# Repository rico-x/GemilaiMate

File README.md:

# GemilaiMate

**Gemilai 3007Z · carrier v0.1 / shield v0.2.4 / Compact 0.3.1 · firmware v0.1.0 · Rico-X**

> **Проект пока не воспроизводился в железе. Ни одна плата не изготовлена и не собрана, USB-прошивка на реальных модулях и работа в кофемашине не проверялись. Успешные сборки, тесты и ERC/DRC относятся только к файлам и программным моделям.**

Самостоятельный проект адаптации управления проливом Gemilai 3007Z: ESP32-S3, LilyGo T-RGB 2.1, давление через ADS1115, термопара MAX31855, управление помпой через RobotDyn и клапаном через внешний SSR. Предполагается сохранение штатного управления нагревом и паром; применимость к конкретной машине ещё требует проверки. Сеть 230 В ни на одну из плат не заходит.

**Сайт проекта: [rico-x.github.io/GemilaiMate](https://rico-x.github.io/GemilaiMate/)** — все платы, схемы подключения с 3D, закупка и пошаговый монтаж Compact.

Разводка, исходники и производственные файлы находятся в этом репозитории; исходный проект не требуется для сборки. Обновления извне автоматически не подтягиваются, нужные изменения переносятся вручную после проверки.

## Три варианта платы

Варианты независимы: у каждого свой KiCad-проект и производственный комплект. GPIO и логика прошивки общие, отличаются компоновка, контроллер и способ сборки.

| | [Carrier v0.1](#carrier-v01) | [Shield v0.2.4](#shield-v024) | [Compact 0.3.1](#compact-031) |
|---|---|---|---|
| Текстолит | 90×46 мм, 2 слоя | 90×75 мм, 2 слоя | 76×61 мм, 2 слоя + антенна 7 мм |
| Контроллер | ESP32-S3 DevKit N8R8 в гнёздах | ESP32-S3 DevKit N8R8 в гнёздах | ESP32-S3-WROOM-1-N16R8 на плате |
| ADS1115 / MAX31855 / TXS0102 | на жгутах | в гнёздах | в гнёздах |
| Жгуты базовой машины | 9 жгутов, 37 проводов | 6 жгутов, 18 проводов | 6 жгутов, 18 проводов |
| SMD | 20 | 20 | 77, в том числе WROOM и USB-C |
| Цель прошивки | `controller`, ID=3 | `controller`, ID=3 | `controller-compact`, ID=4 |
| Подключение и 3D | [wiring.html](https://rico-x.github.io/GemilaiMate/wiring.html) | [shield-wiring.html](https://rico-x.github.io/GemilaiMate/shield-wiring.html) | [compact-wiring.html](https://rico-x.github.io/GemilaiMate/compact-wiring.html) |

## Carrier v0.1

Исходная плата 90×46 мм: DevKit в гнёздах, измерительные и силовые модули подключаются жгутами. Плата не изменялась с первого выпуска.

- [Подключение в машине: схема, 3D и жгуты](https://rico-x.github.io/GemilaiMate/wiring.html) ([файл](docs/wiring.html)).
- [Сборка и крепление](docs/assembly.md), [интерфейсы платы](docs/interfaces.md), [корпуса жгутов](docs/harnesses.md).
- [Комплектующие](docs/components.md) и [пример закупки комплекта](docs/purchase-kit.md).
- KiCad: [`hardware/carrier/gemilaimate-carrier.kicad_pro`](hardware/carrier/gemilaimate-carrier.kicad_pro). Производство: [Gerber/Excellon, BOM, CPL](hardware/carrier/manufacturing/). Шаблон: [`mounting-template-1to1.pdf`](hardware/carrier/mounting-template-1to1.pdf).

Жгуты J5/J6 собирать в цельных маркированных корпусах по [таблице](docs/harnesses.md): у carrier J5 — 1×4, J6 — 1×3, гнездовые контакты. Корпуса без механического ключа: разворот на 180° возможен, перед питанием нужна проверка ориентации и прозвонка. Перед изготовлением сверить реальный ESP32 с шаблоном и просвет ≥5 мм под ним.

## Shield v0.2.4

Плата 90×75 мм: в неё напрямую вставляются DevKit, ADS1115, TXS0102 и MAX31855 — вместо трёх жгутов. RobotDyn и SSR закрепляются отдельно и подключаются управляющими жгутами 4+3 жилы; прямая стыковка силовых модулей не предусмотрена. Shield не заменяет carrier.

- [Рендеры, маркировка, шаблон 1:1 и распиновка](https://rico-x.github.io/GemilaiMate/shield.html) ([файл](docs/shield.html)).
- [Подключение shield: схема, 3D и жгуты](https://rico-x.github.io/GemilaiMate/shield-wiring.html) ([файл](docs/shield-wiring.html)).
- [Сборка, ориентация и ограничения](docs/shield.md), [держатель с прижимами](docs/retention.md) (ещё не изготовлен и не примерен).
- KiCad: [`hardware/shield/gemilaimate-shield.kicad_pro`](hardware/shield/gemilaimate-shield.kicad_pro). Производство: [Gerber ZIP, BOM, CPL](hardware/shield/manufacturing/). Шаблон: [`mounting-template-1to1.svg`](hardware/shield/mounting-template-1to1.svg).

Ориентация гнёзд отмечена на PCB. Ответные колодки и крепёж проверены только по номинальным допускам. У shield и carrier разные пол контактов и корпус J6 — таблицы жгутов не взаимозаменяемы.

## Compact 0.3.1

Самая маленькая плата: 76×61 мм, два слоя. ESP32-S3-WROOM-1-N16R8 и собственный USB-C (только для прошивки) распаяны на плате; ADS1115, MAX31855 и CJMCU-0102 вставляются в гнёзда сверху, все кабельные JST PH/XH — снизу. Посадочные места рассчитаны на ручную пайку: 0805/1206, SOT-23, SOIC. Определение платы соответствует GaggiMate Pro PCB Rev 1.1 (ID=4). ERC/DRC и воспроизводимая пересборка пройдены; переключение официальной и собственной прошивки не испытывалось.

- [Обзор: рендеры, сборочные виды, распиновка разъёмов](https://rico-x.github.io/GemilaiMate/compact.html) ([файл](docs/compact.html)).
- [Подключение: схема, 3D и жгуты](https://rico-x.github.io/GemilaiMate/compact-wiring.html) ([файл](docs/compact-wiring.html)).
- [Gemilai 3007Z: гидравлика с двумя трёхходовыми клапанами и подключение Compact](https://gemilaimate-3007z-wiring.wiseparrot.chatgpt.site/) (закрытая страница Sites, [копия HTML в репозитории](docs/gemilai-3007z-hydraulics.html)).
- [Закупка с расчётом количества](https://rico-x.github.io/GemilaiMate/compact-purchase.html) ([файл](docs/compact-purchase.html)) и [что докупить к прежнему комплекту](docs/compact-purchase-delta.md).
- [Пошаговый монтаж с картами позиций](https://rico-x.github.io/GemilaiMate/compact-assembly.html) ([текстовая версия](docs/compact-assembly.md)).
- [Описание, допуски, питание, GPIO и приёмка](docs/compact-shield.md), [требования](docs/plans/compact-shield.md), [размеры компонентов](docs/component-dimensions.md).
- KiCad: [`hardware/shield-compact/gemilaimate-compact.kicad_pro`](hardware/shield-compact/gemilaimate-compact.kicad_pro). Производство: [Gerber ZIP, BOM, CPL, жгуты](hardware/shield-compact/manufacturing/). Печать 1:1: [сверху](hardware/shield-compact/previews/assembly-1to1.pdf), [снизу](hardware/shield-compact/previews/assembly-bottom-1to1.pdf).

Прошивка — цель `controller-compact` из текущих исходников; старый релиз v0.1.0 её не содержит. Самые трудные места ручной сборки — центральная земля WROOM и USB-C с шагом 0,5 мм. Реальные модули-клоны не замерены: до заказа приложить их к печати 1:1.

## Начать здесь

1. [Статус проверок и открытые вопросы](docs/validation.md), [совместимость](docs/compatibility.md).
2. Выбрать плату и пройти её раздел выше: подключение, закупка, сборка.
3. [Низковольтный стенд](docs/bench.md) и [прошивка через USB](docs/flashing.md) — до установки в машину.
4. [Производство и бюджет](docs/manufacturing.md).
5. [Сборка исходников и сопровождение](docs/development.md).

Общая прошивка carrier и shield: [релиз v0.1.0](https://github.com/Rico-X/GemilaiMate/releases/tag/v0.1.0). Сетевое OTA отключено; устанавливать согласованную пару controller/display через USB.

| Путь | Содержание |
|---|---|
| `firmware/` | Код контроллера, дисплея, веб-интерфейса, протокол и текущие тесты |
| `hardware/carrier/` | Carrier v0.1 90×46 с жгутами; исходная плата без изменений |
| `hardware/shield/` | Shield v0.2.4 90×75 с модульными гнёздами; отдельные KiCad, Gerber/BOM, SVG 1:1 |
| `hardware/shield-compact/` | Compact 0.3.1: KiCad, схема, проверки, рендеры и опытный производственный комплект; N16R8, без DevKit |
| `tools/` | Сборка релиза, генераторы страниц, проверки, host-тесты и проверяющий прошивальщик |
| `docs/` | Документация текущей версии и страницы GitHub Pages |

Адаптация под Gemilai, платы и сопровождение: **Rico-X**. Код основан на GaggiMate авторства jniebuhr и участников проекта; изменения и лицензии указаны в [NOTICE](NOTICE.md) и [LICENSE](LICENSE.md). Это независимая адаптация, без заявления о проверенной совместимости или одобрении исходными авторами.

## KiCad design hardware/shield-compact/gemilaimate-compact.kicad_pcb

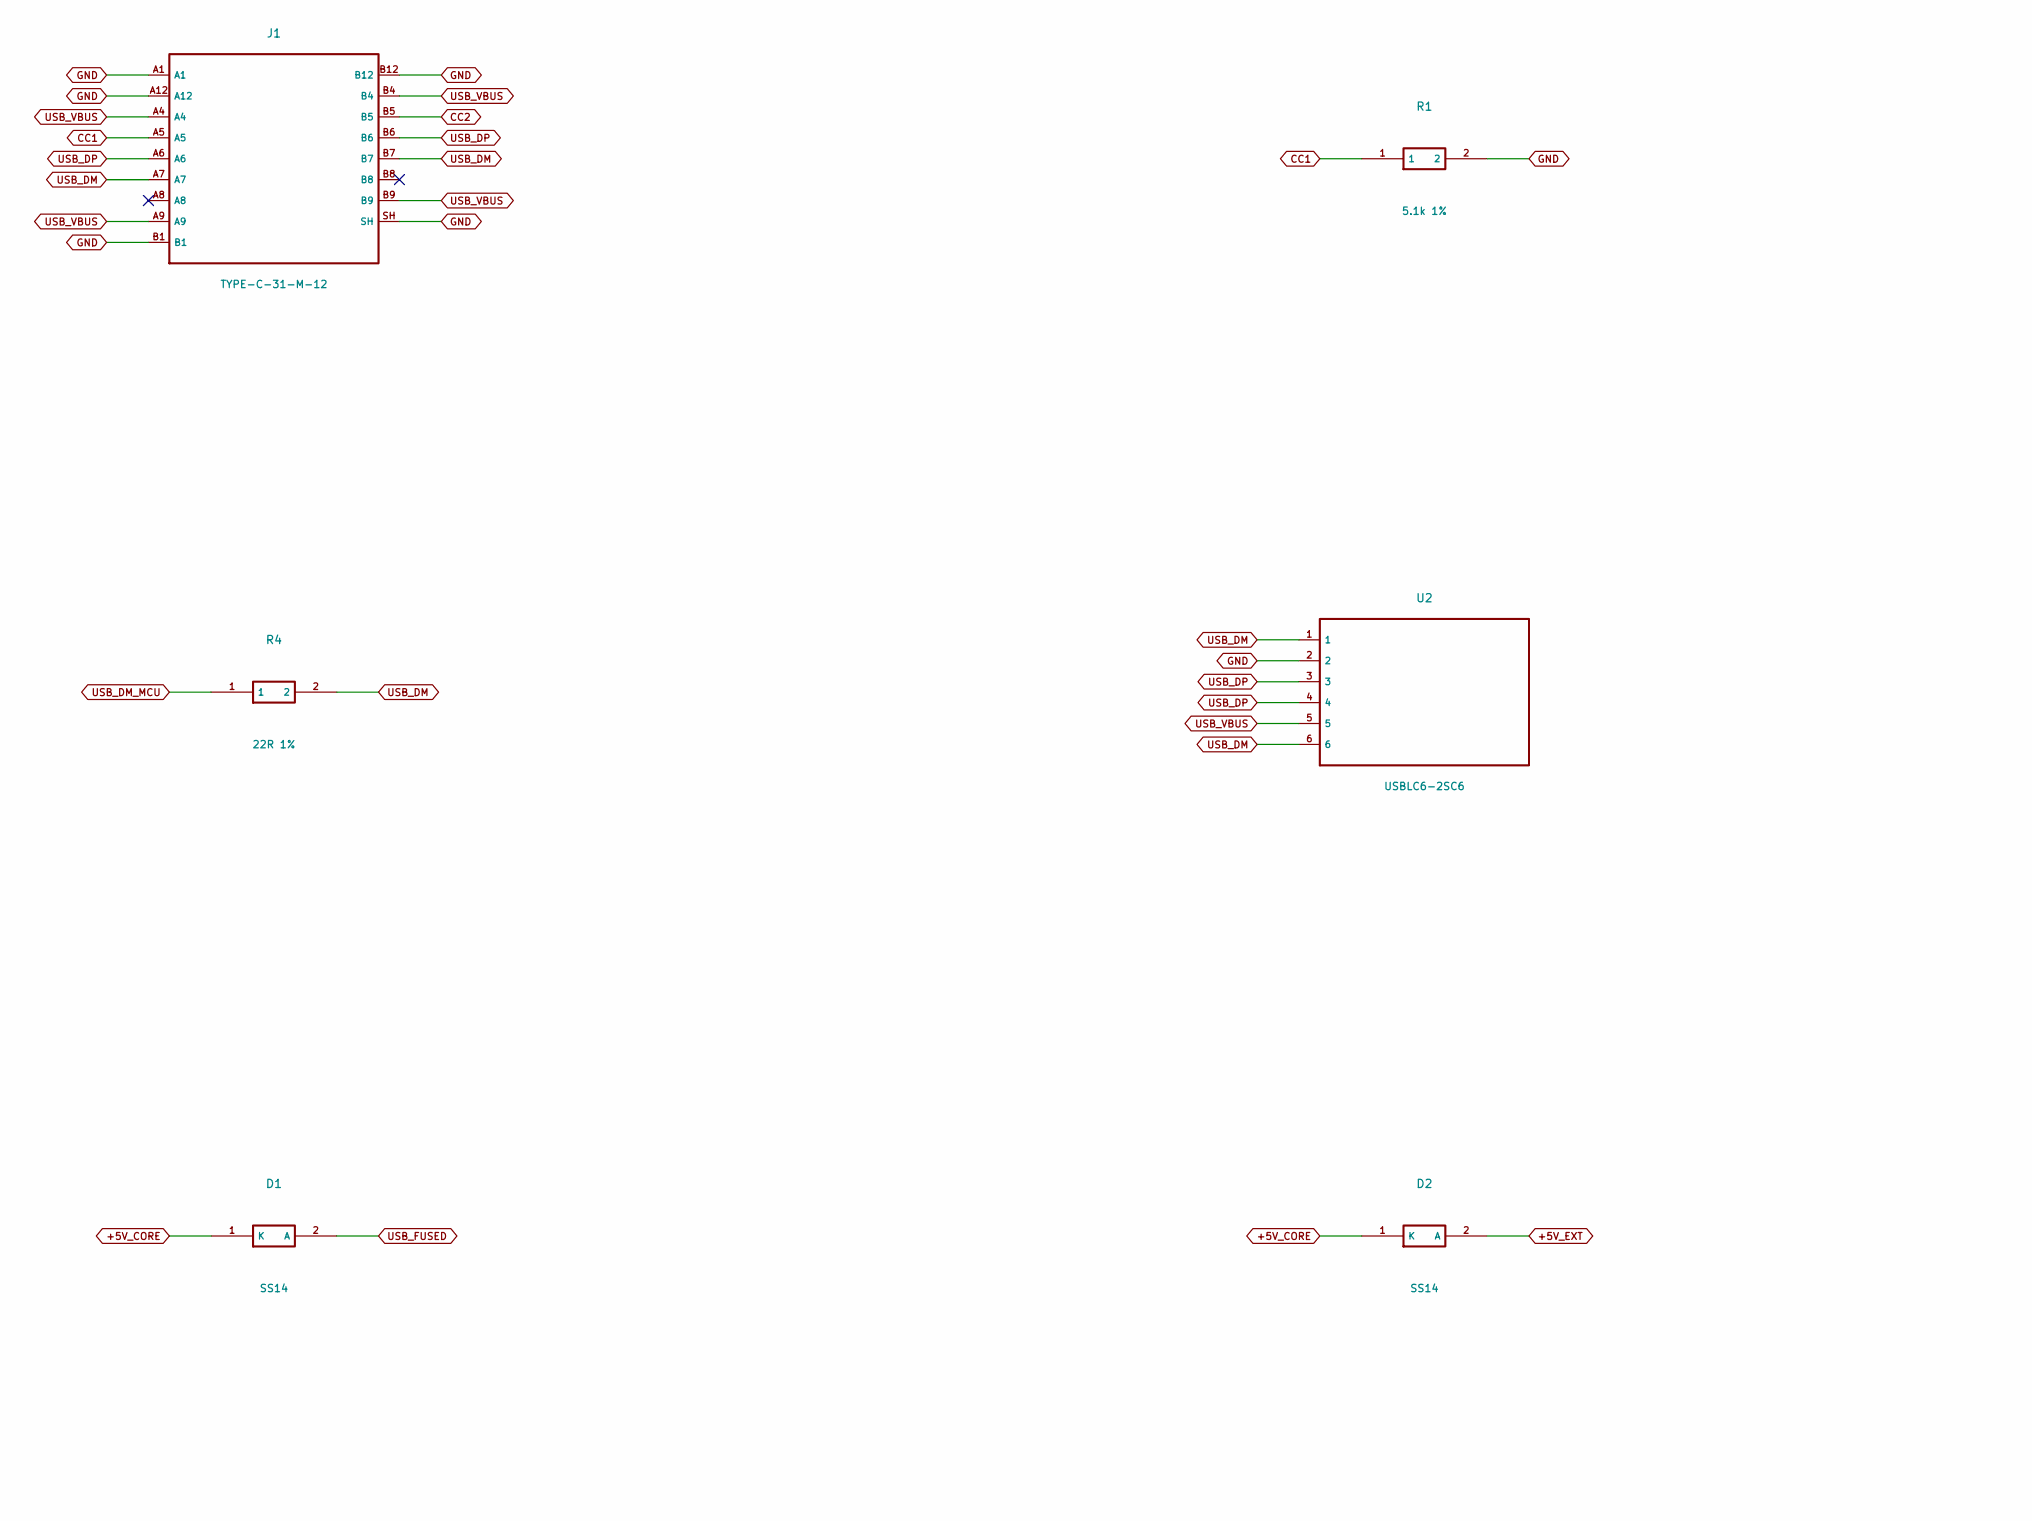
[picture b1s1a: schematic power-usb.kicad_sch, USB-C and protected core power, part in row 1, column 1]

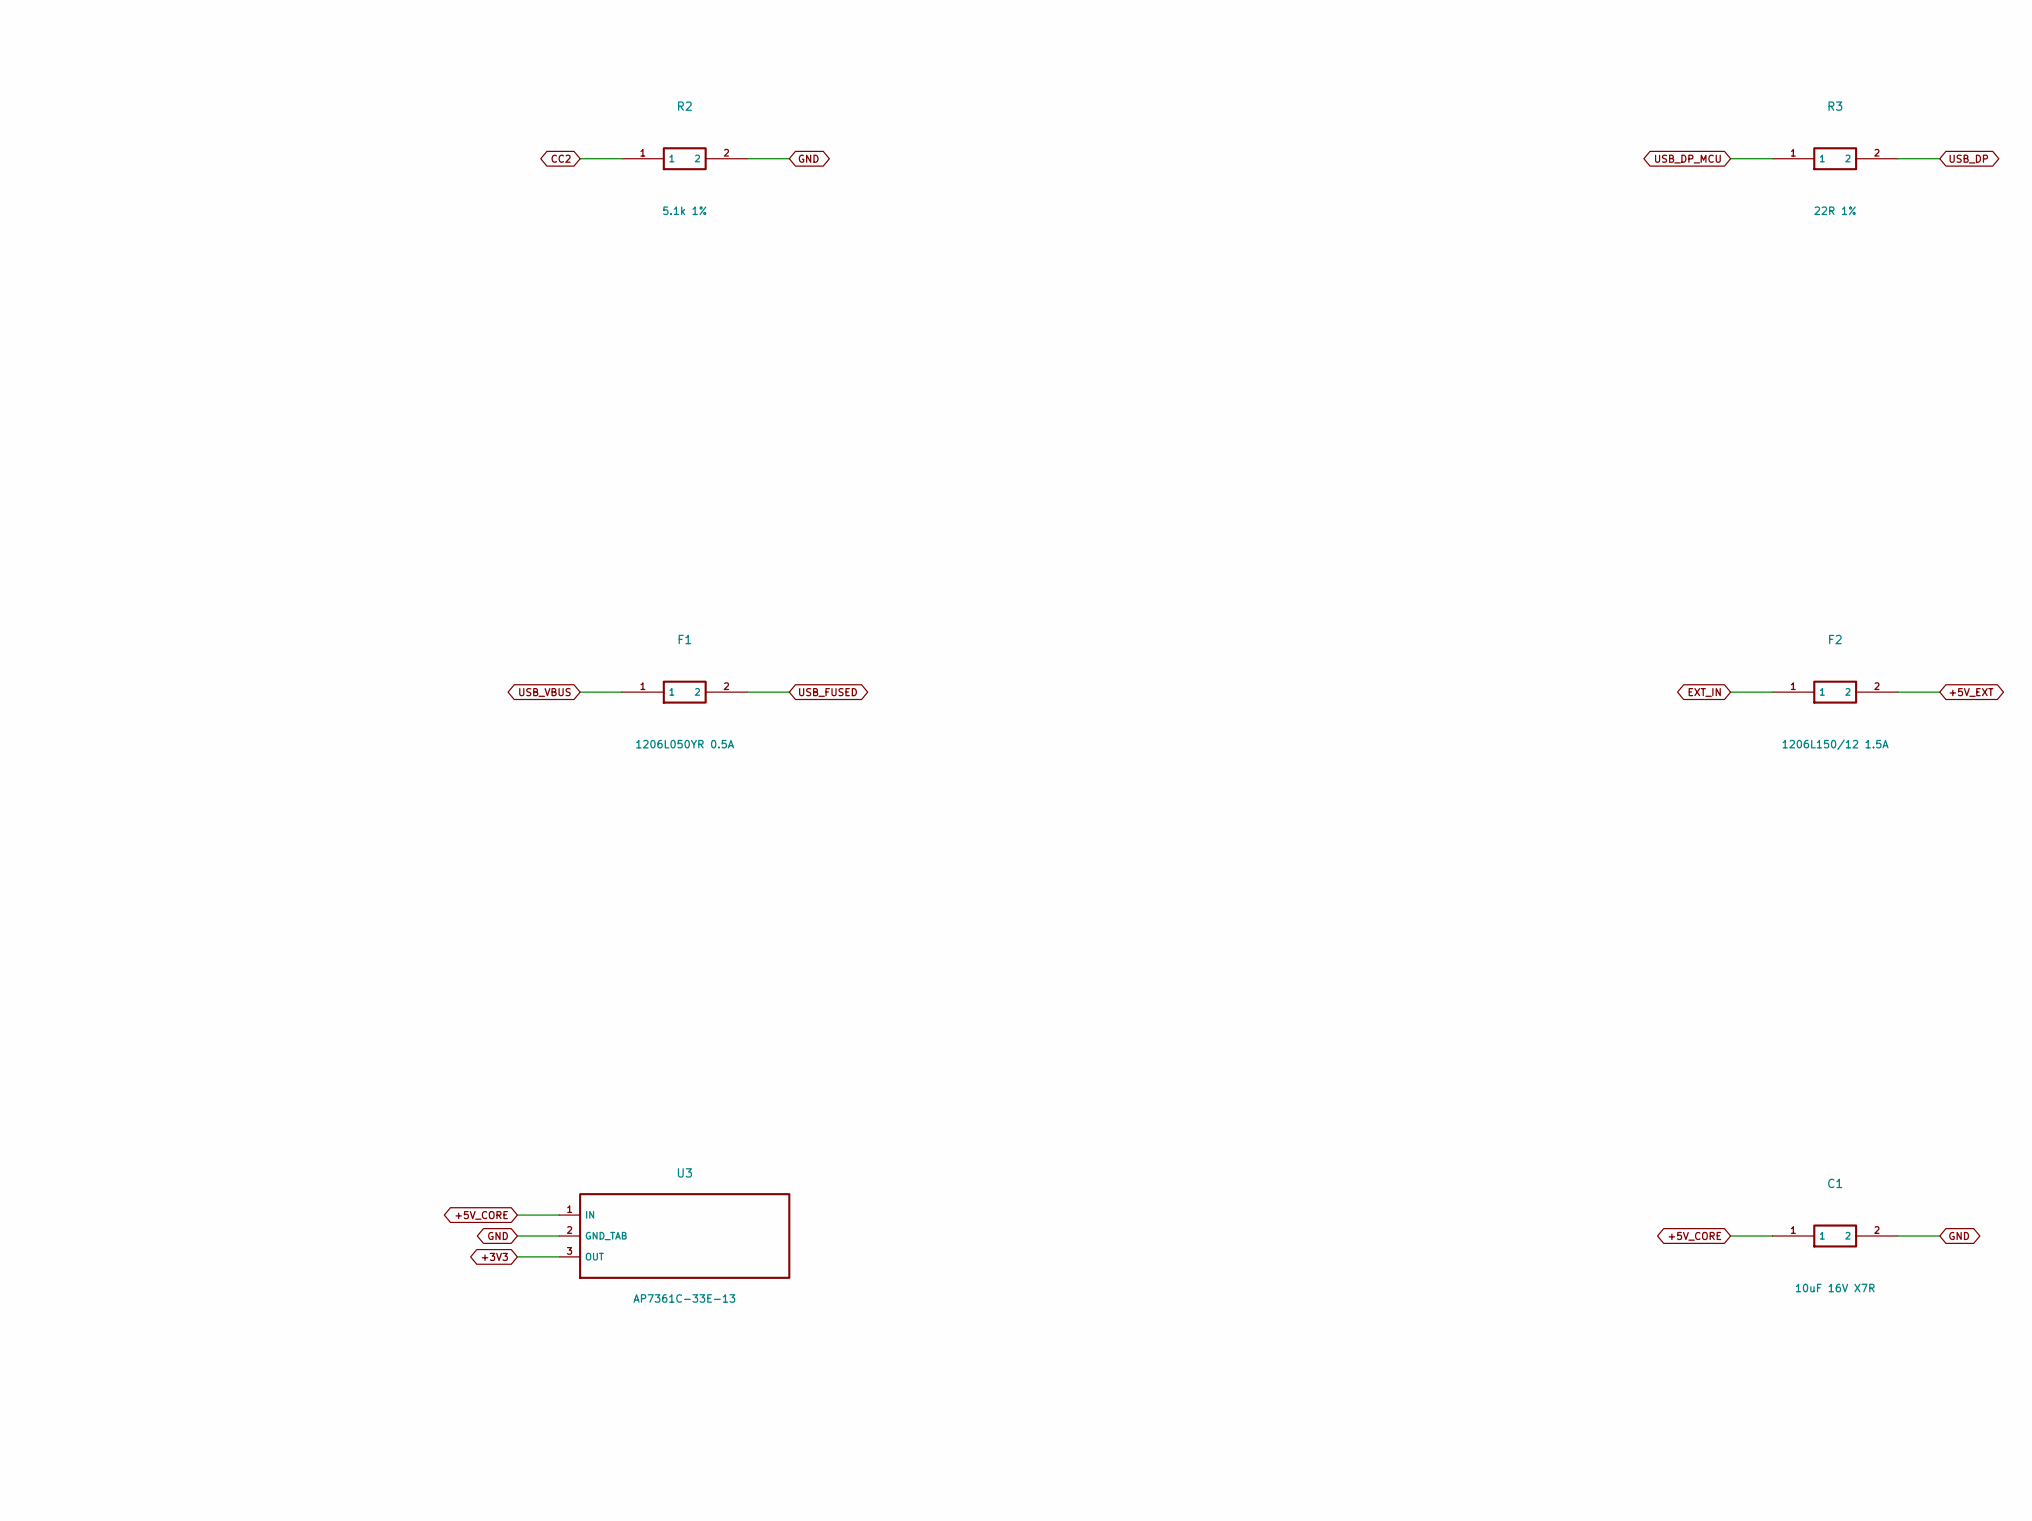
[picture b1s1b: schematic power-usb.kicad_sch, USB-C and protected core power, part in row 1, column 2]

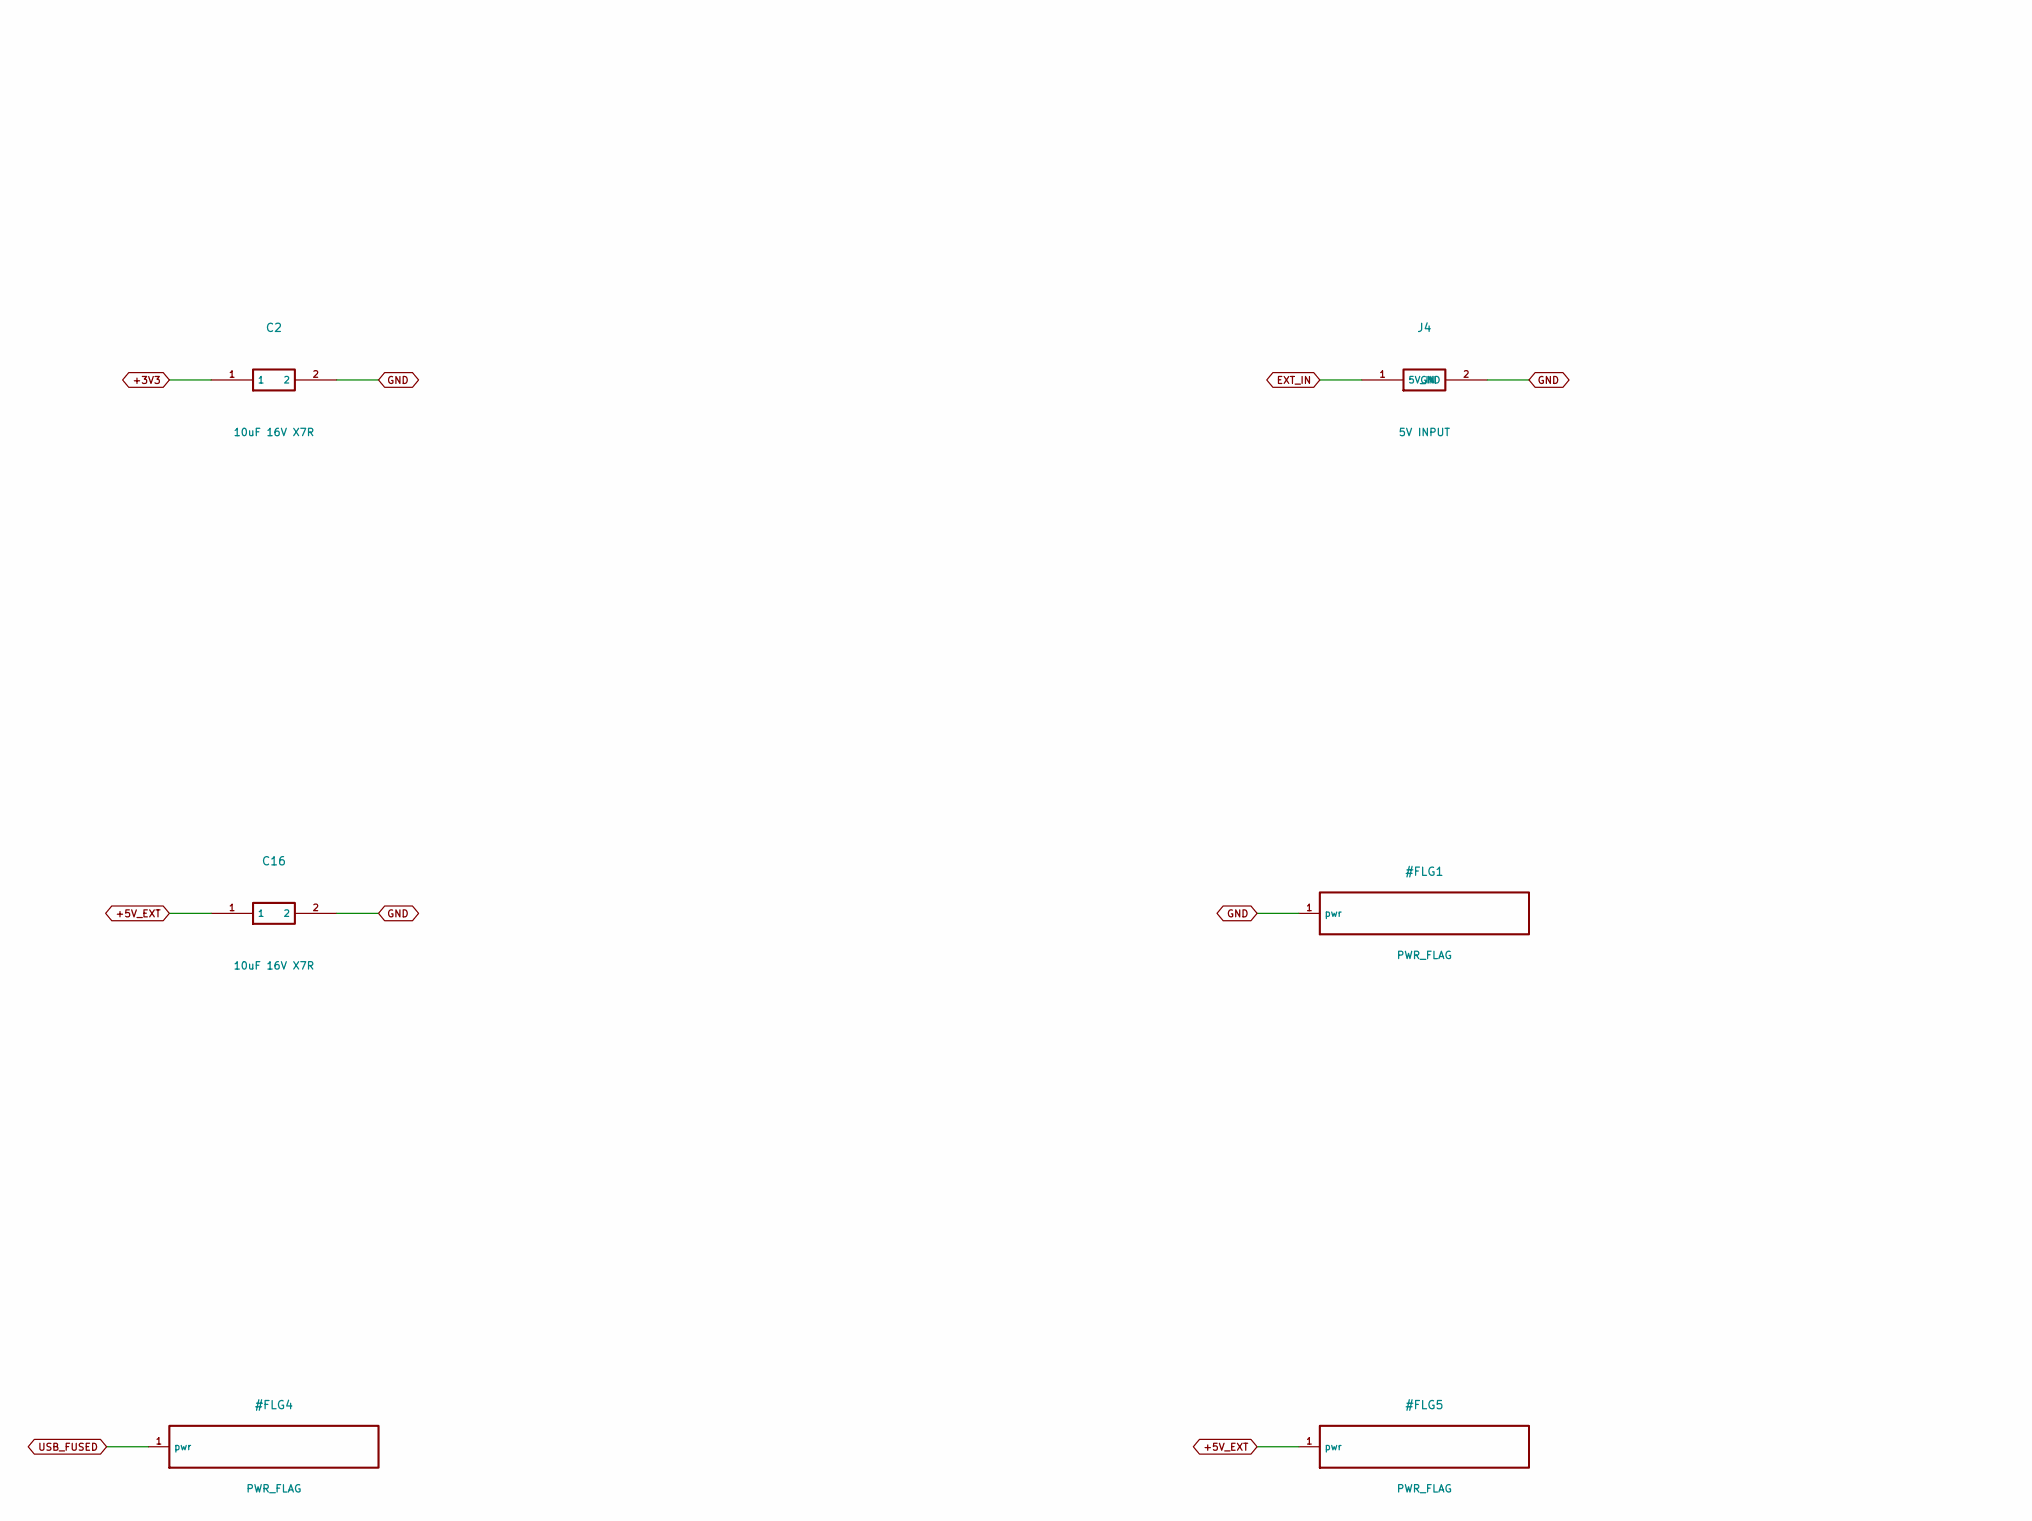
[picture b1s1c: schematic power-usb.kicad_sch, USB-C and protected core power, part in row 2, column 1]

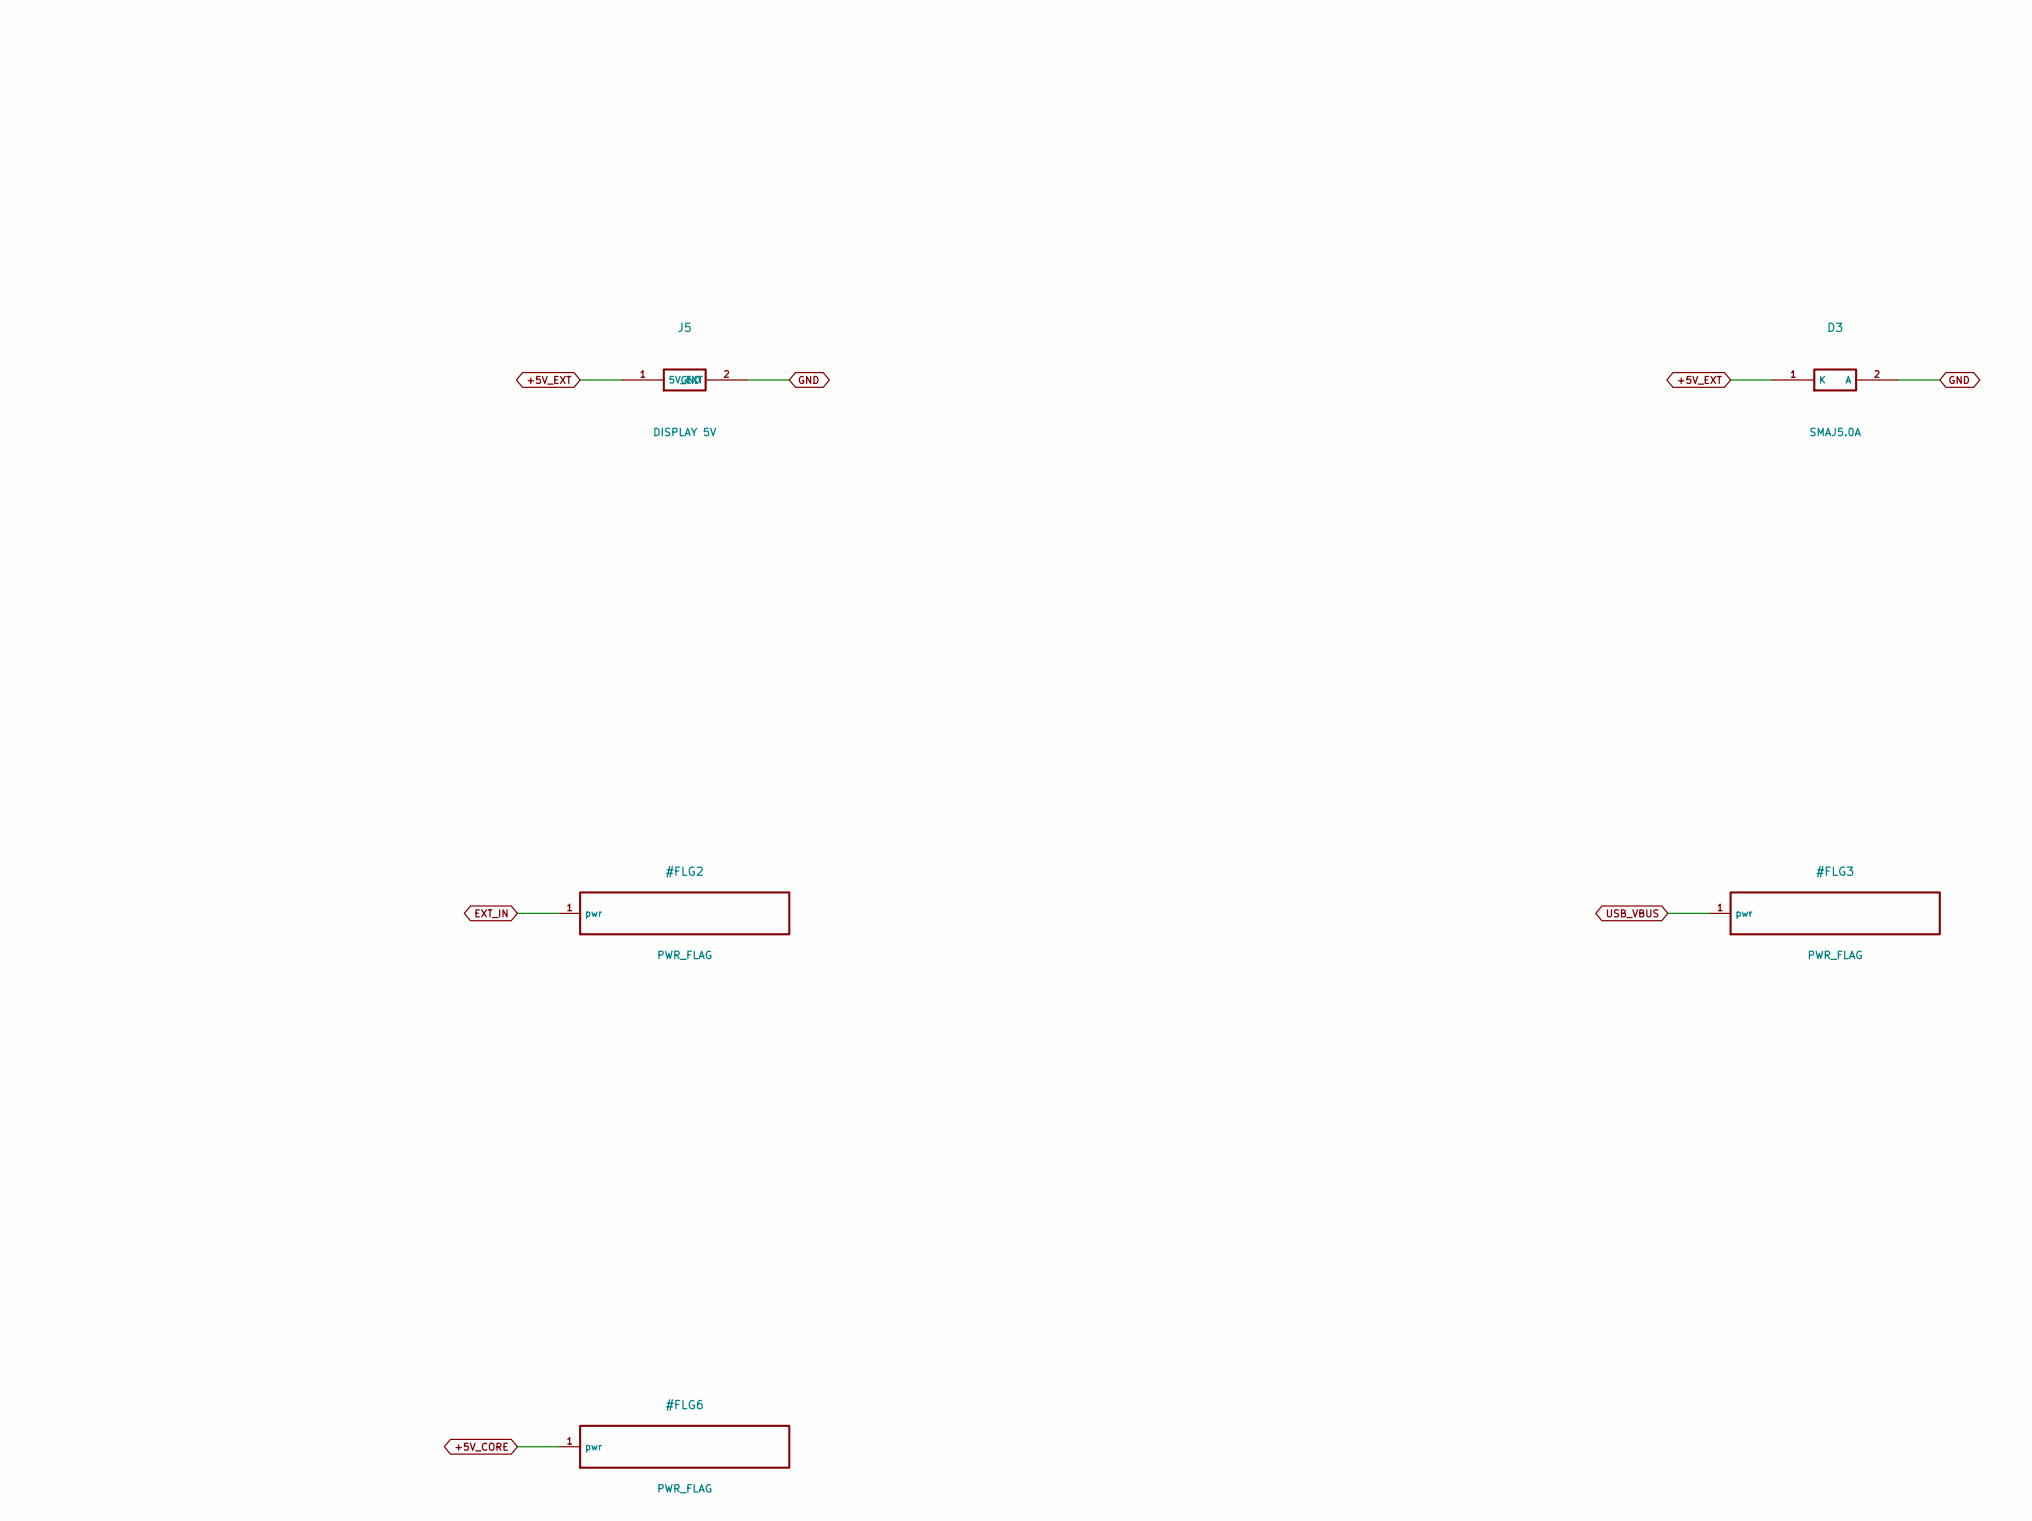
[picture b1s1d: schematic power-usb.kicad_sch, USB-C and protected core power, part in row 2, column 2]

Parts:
C1, C2, C16: 10uF 16V X7R; C_1206_3216Metric_Pad1.33x1.80mm_HandSolder
D1, D2: SS14; D_SMA_Handsoldering
D3: SMAJ5.0A; D_SMA_Handsoldering
F1: 1206L050YR 0.5A; Fuse_1206_3216Metric_Pad1.42x1.75mm_HandSolder
F2: 1206L150/12 1.5A; Fuse_1206_3216Metric_Pad1.42x1.75mm_HandSolder
J1: TYPE-C-31-M-12; USB_C_Receptacle_HRO_TYPE-C-31-M-12
J4: 5V INPUT; JST_XH_B2B-XH-A_1x02_P2.50mm_Vertical
J5: DISPLAY 5V; JST_PH_B2B-PH-K_1x02_P2.00mm_Vertical
R1, R2: 5.1k 1%; R_0805_2012Metric_Pad1.20x1.40mm_HandSolder
R3, R4: 22R 1%; R_0805_2012Metric_Pad1.20x1.40mm_HandSolder
U2: USBLC6-2SC6; SOT-23-6_Handsoldering
U3: AP7361C-33E-13; SOT-223-3_TabPin2

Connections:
+3V3: C2.1, U3.3 (OUT); also elsewhere on the board
+5V_CORE: C1.1, D1.1 (K), D2.1 (K), U3.1 (IN); also elsewhere on the board
+5V_EXT: C16.1, D2.2 (A), D3.1 (K), F2.2, J5.1 (5V_EXT); also elsewhere on the board
CC1: J1.A5, R1.1
CC2: J1.B5, R2.1
EXT_IN: F2.1, J4.1 (5V_IN)
GND: C1.2, C2.2, C16.2, D3.2 (A), J1.A1, J1.A12, J1.B1, J1.B12, J1.SH, J4.2 (GND), J5.2 (GND), R1.2, R2.2, U2.2, U3.2 (GND_TAB); also elsewhere on the board
USB_DM: J1.A7, J1.B7, R4.2, U2.1, U2.6
USB_DM_MCU: R4.1; also elsewhere on the board
USB_DP: J1.A6, J1.B6, R3.2, U2.3, U2.4
USB_DP_MCU: R3.1; also elsewhere on the board
USB_FUSED: D1.2 (A), F1.2
USB_VBUS: F1.1, J1.A4, J1.A9, J1.B4, J1.B9, U2.5
